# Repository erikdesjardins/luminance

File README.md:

# luminance

AKA "light destroyer". High voltage switching current supply.

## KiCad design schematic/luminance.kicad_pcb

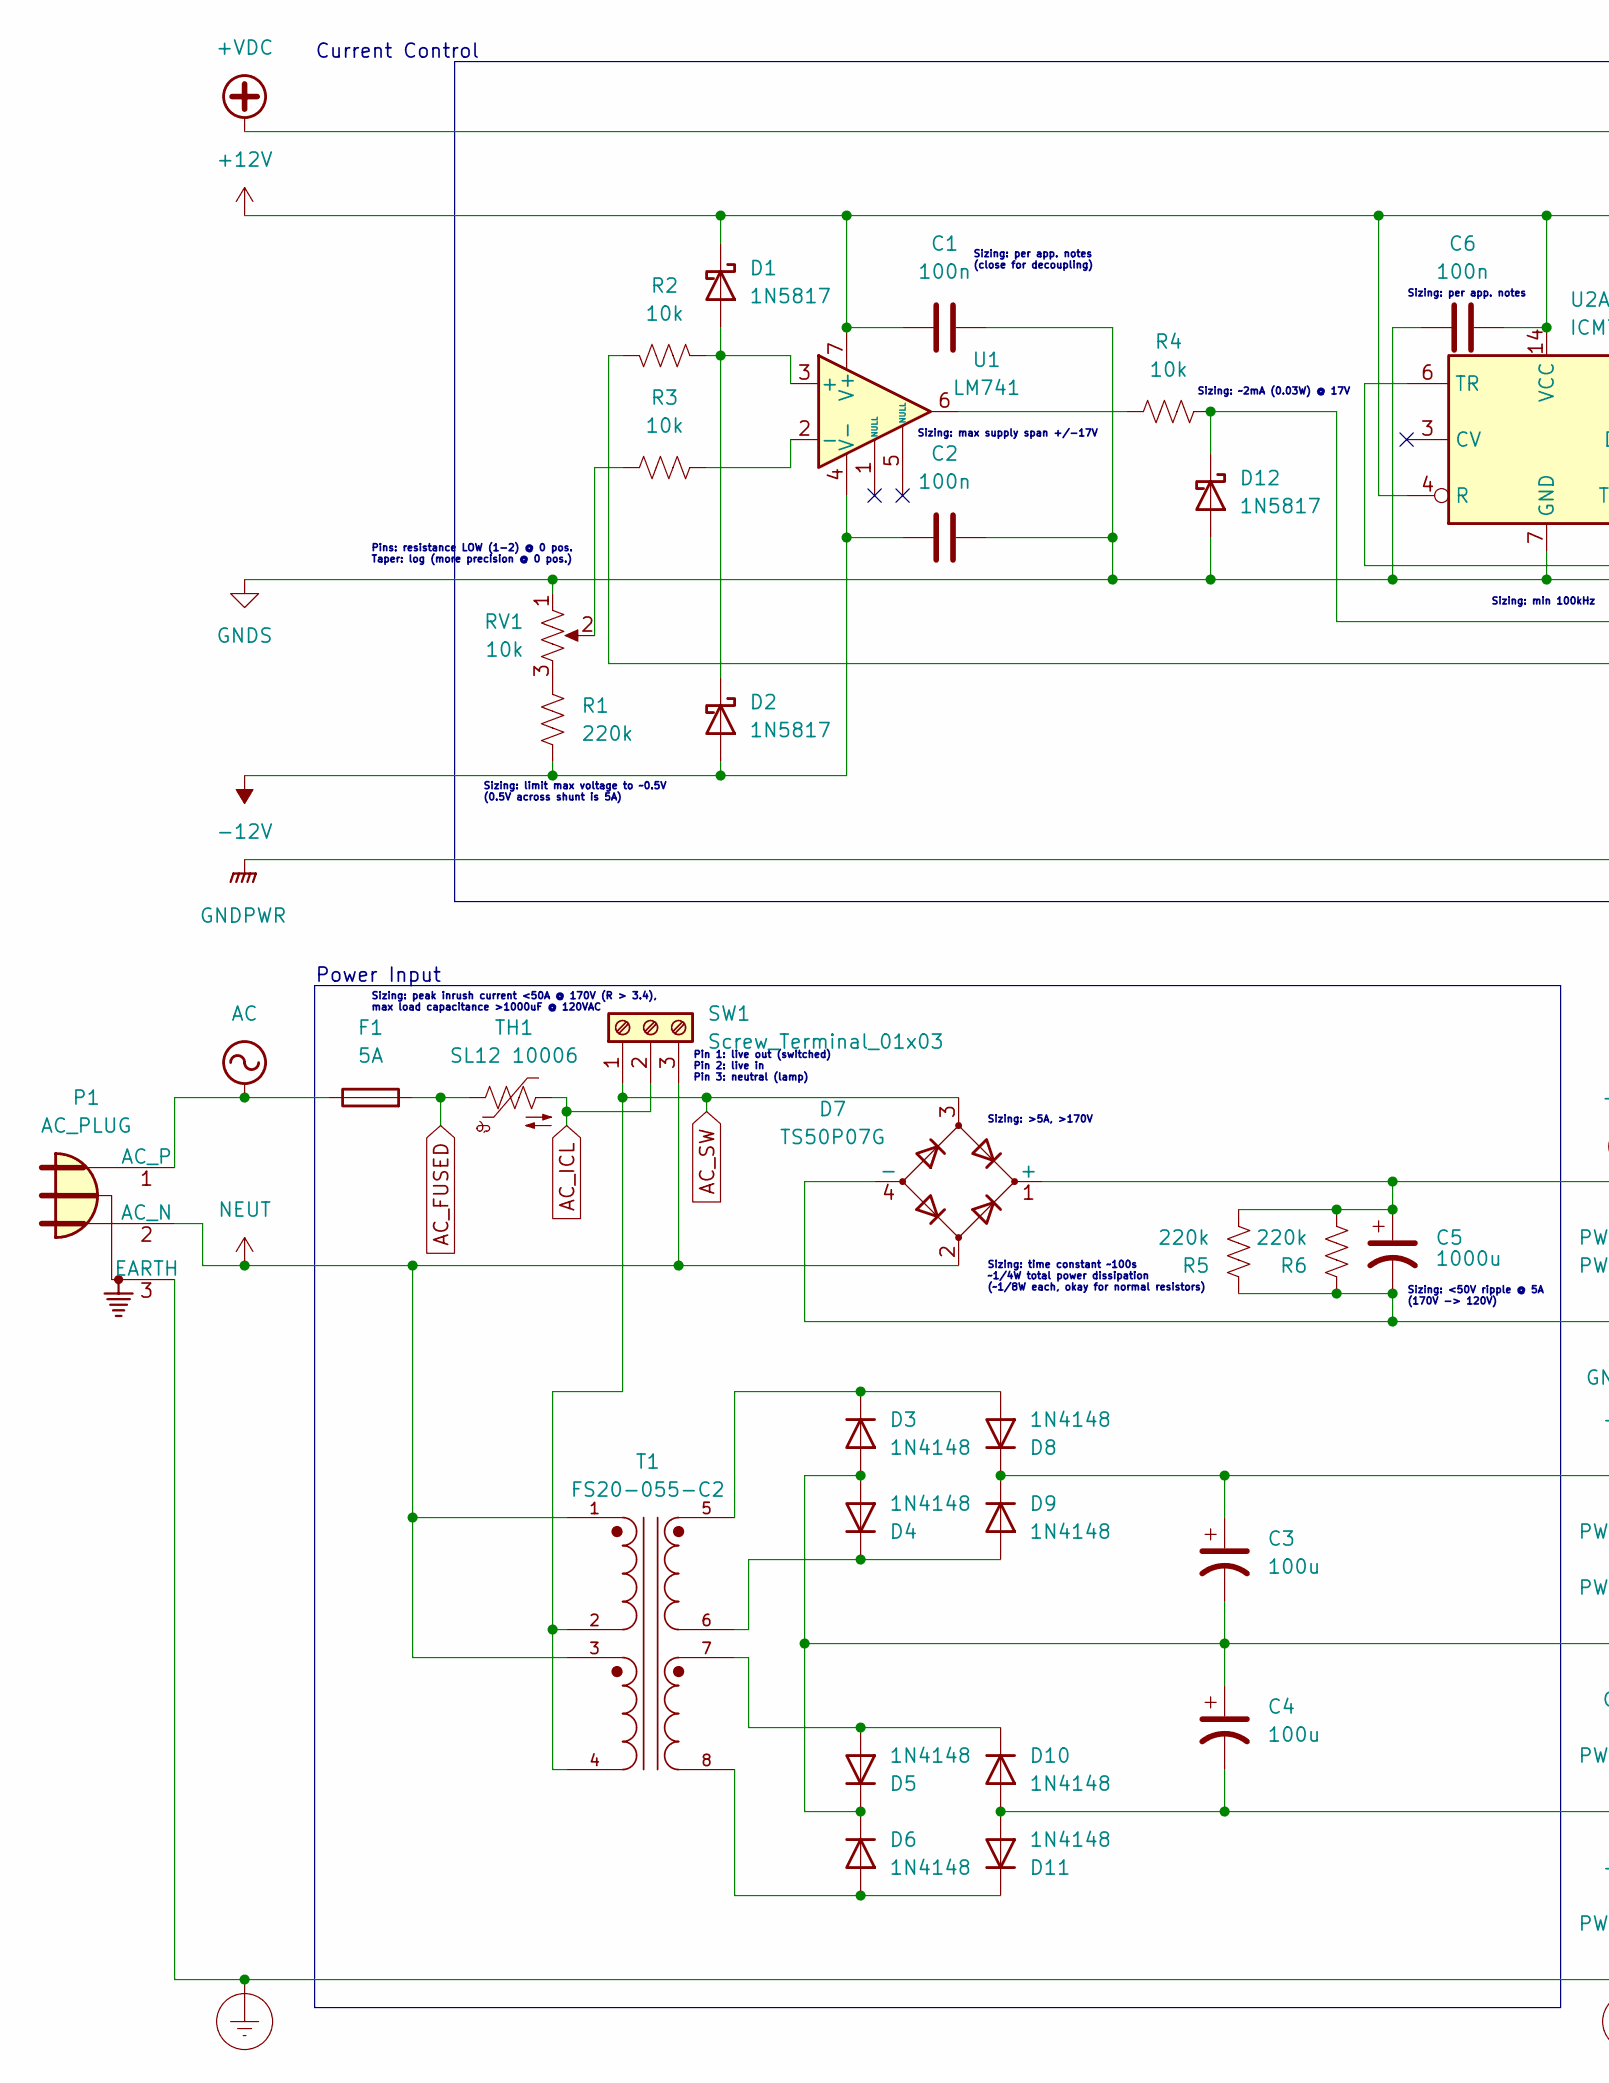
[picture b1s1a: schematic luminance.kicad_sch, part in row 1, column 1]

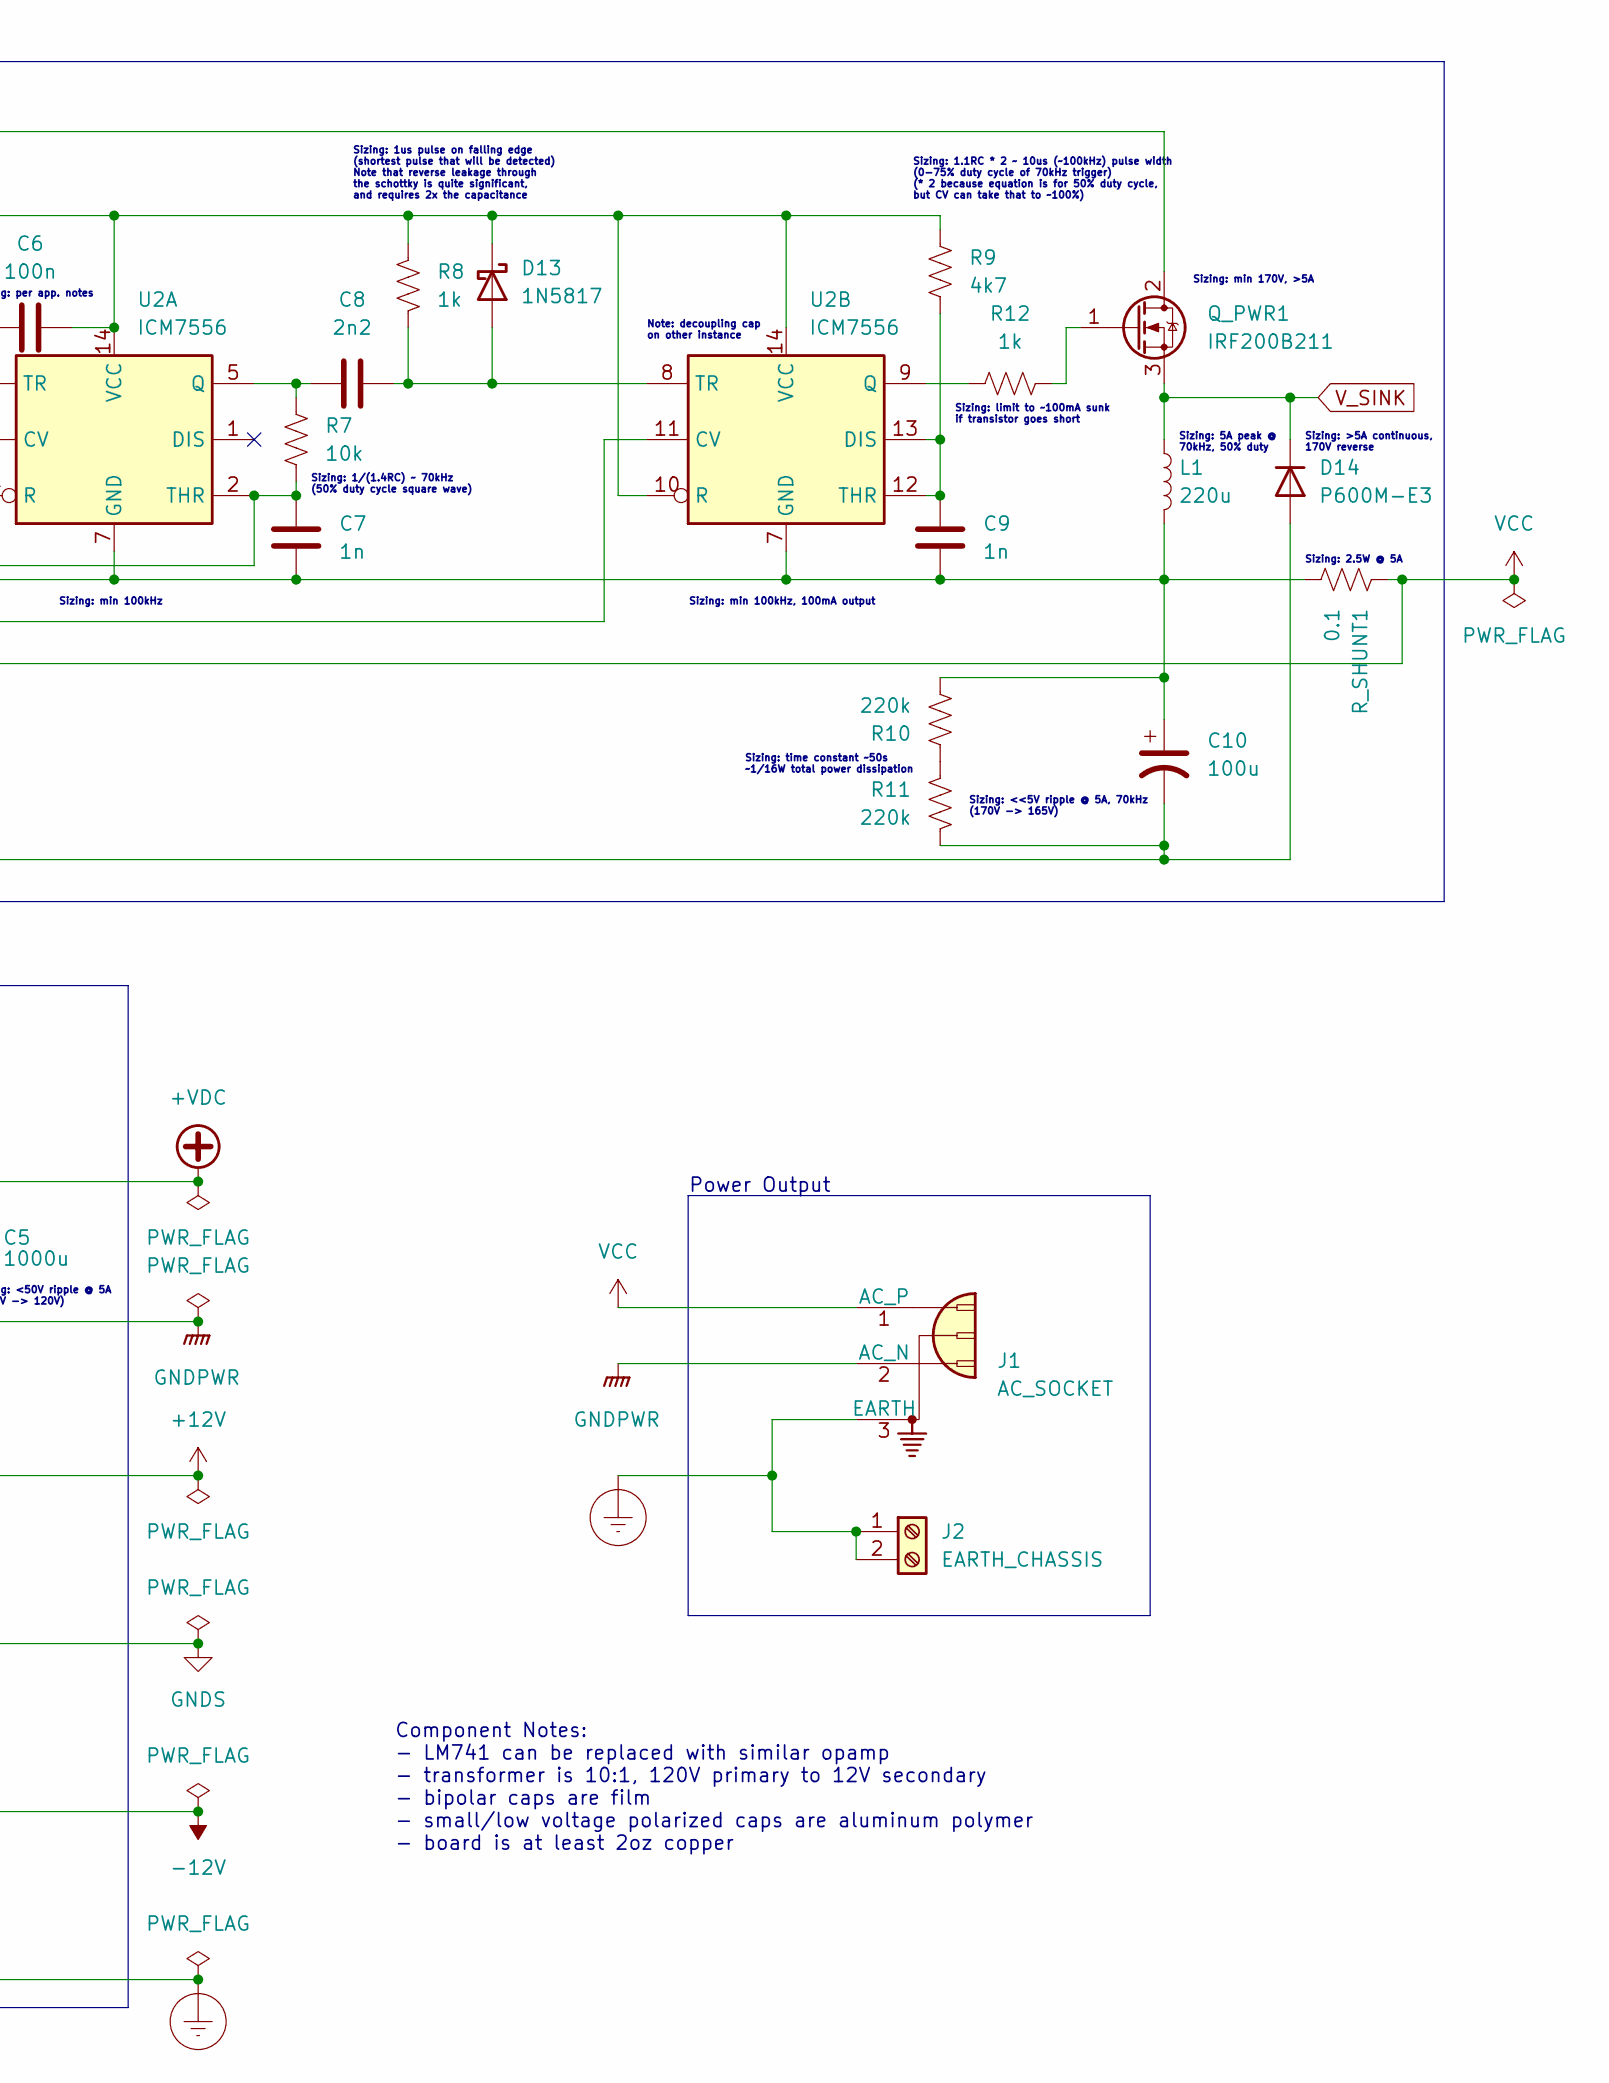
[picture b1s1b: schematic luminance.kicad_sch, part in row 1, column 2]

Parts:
C1, C2, C6: 100n; C_Rect_L7.2mm_W2.5mm_P5.00mm_FKS2_FKP2_MKS2_MKP2
C3, C4: 100u; CP_Radial_D8.0mm_P3.50mm
C5: 1000u; CP_Radial_D30.0mm_P10.00mm_SnapIn
C7, C9: 1n; C_Rect_L7.2mm_W2.5mm_P5.00mm_FKS2_FKP2_MKS2_MKP2
C8: 2n2; C_Rect_L7.2mm_W2.5mm_P5.00mm_FKS2_FKP2_MKS2_MKP2
C10: 100u; CP_Radial_D16.0mm_P7.50mm
D1, D2, D12, D13: 1N5817; D_DO-41_SOD81_P10.16mm_Horizontal
D3, D4, D5, D6, D8, D9, D10, D11: 1N4148; D_DO-35_SOD27_P7.62mm_Horizontal
D7: TS50P07G; DIOB_TS50P07G
D14: P600M-E3; P600
F1: 5A; 696106003002
J1: AC_SOCKET; TerminalBlock_Phoenix_PT-1,5-3-5.0-H_1x03_P5.00mm_Horizontal
J2: EARTH_CHASSIS; TerminalBlock_Phoenix_PT-1,5-2-5.0-H_1x02_P5.00mm_Horizontal
L1: 220u; L_Toroid_Vertical_L31.8mm_W15.9mm_P13.50mm_Bourns_5700
P1: AC_PLUG; TerminalBlock_Phoenix_PT-1,5-3-5.0-H_1x03_P5.00mm_Horizontal
Q_PWR1: IRF200B211; TO-220-3_Vertical
R1, R5, R6, R10, R11: 220k; R_Axial_DIN0204_L3.6mm_D1.6mm_P7.62mm_Horizontal
R2, R3, R4, R7: 10k; R_Axial_DIN0204_L3.6mm_D1.6mm_P7.62mm_Horizontal
R8, R12: 1k; R_Axial_DIN0204_L3.6mm_D1.6mm_P7.62mm_Horizontal
R9: 4k7; R_Axial_DIN0204_L3.6mm_D1.6mm_P7.62mm_Horizontal
RV1: 10k; TerminalBlock_Phoenix_PT-1,5-3-5.0-H_1x03_P5.00mm_Horizontal
R_SHUNT1: 0.1; R_Shunt_Vishay_SR3_P15.24mm_Horizontal
SW1: Screw_Terminal_01x03; TerminalBlock_Phoenix_PT-1,5-3-5.0-H_1x03_P5.00mm_Horizontal
T1: FS20-055-C2; XFMR_FS20-055-C2; PARTREV N/A
TH1: SL12 10006; C_Disc_D12.5mm_W5.0mm_P7.50mm
U1: LM741; DIP-8_W7.62mm_Socket
U2: ICM7556; DIP-14_W7.62mm_Socket

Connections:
+12V: C1.2, C3.1, C6.2, D1.1 (K), D8.1 (K), D9.1 (K), D13.1 (K), R8.1, R9.1, U1.7 (V+), U2.4 (R), U2.10 (R), U2.14 (VCC)
+VDC: C5.1, D7.1 (+), Q_PWR1.2 (D), R5.2, R6.2
-12V: C2.1, C4.2, D2.2 (A), D10.2 (A), D11.2 (A), R1.1, U1.4 (V-)
AC: F1.1, P1.1 (AC_P)
AC_FUSED: F1.2, TH1.1
AC_ICL: SW1.2, TH1.2
AC_SW: D7.3, SW1.1, T1.2, T1.4
Earth_Protective: J1.3 (EARTH), J2.1, J2.2, P1.3 (EARTH)
GNDPWR: C5.2, C10.2, D7.4 (-), D14.2 (A), J1.2 (AC_N), R5.1, R6.1, R11.2
GNDS: C1.1, C2.2, C3.2, C4.1, C6.1, C7.1, C9.2, C10.1, D3.2 (A), D4.2 (A), D5.1 (K), D6.1 (K), D12.2 (A), L1.2, R10.2, RV1.1, R_SHUNT1.2, U2.7 (GND)
NEUT: D7.2, P1.2 (AC_N), SW1.3, T1.1, T1.3
unnamed: C7.2, R7.1, U2.2 (THR), U2.6 (TR)
unnamed: C8.1, D13.2 (A), R8.2, U2.8 (TR)
unnamed: C8.2, R7.2, U2.5 (Q)
unnamed: C9.1, R9.2, U2.12 (THR), U2.13 (DIS)
unnamed: D1.2 (A), D2.1 (K), R2.1, U1.3 (+)
unnamed: D3.1 (K), D8.2 (A), T1.5
unnamed: D4.1 (K), D9.2 (A), T1.6
unnamed: D5.2 (A), D10.1 (K), T1.7
unnamed: D6.2 (A), D11.1 (K), T1.8
unnamed: D12.1 (K), R4.1, U2.11 (CV)
unnamed: Q_PWR1.1 (G), R12.1
unnamed: R1.2, RV1.3
unnamed: R3.1, U1.2 (-)
unnamed: R3.2, RV1.2
unnamed: R4.2, U1.6
unnamed: R10.1, R11.1
unnamed: R12.2, U2.9 (Q)
VCC: J1.1 (AC_P), R2.2, R_SHUNT1.1
V_SINK: D14.1 (K), L1.1, Q_PWR1.3 (S)

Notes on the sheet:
Sizing: min 170V, >5A
Component Notes: - LM741 can be replaced with similar opamp - transformer is 10:1, 120V primary to 12V secondary - bipolar caps are film - small/low voltage polarized caps are aluminum polymer - board is at least 2oz copper
Sizing: per app. notes
Sizing: limit to ~100mA sunk if transistor goes short
Sizing: >5A continuous, 170V reverse
Sizing: ~2mA (0.03W) @ 17V
Sizing: max supply span +/-17V
Power Output
Sizing: 1/(1.4RC) ~ 70kHz (50% duty cycle square wave)
Pins: resistance LOW (1-2) @ 0 pos. Taper: log (more precision @ 0 pos.)
Current Control
Sizing: 5A peak @ 70kHz, 50% duty
Power Input
Sizing: per app. notes (close for decoupling)
Sizing: <<5V ripple @ 5A, 70kHz (170V -> 165V)
Sizing: >5A, >170V
Sizing: min 100kHz
Sizing: 1us pulse on falling edge (shortest pulse that will be detected) Note that reverse leakage through the schottky is quite significant, and requires 2x the capacitance
Pin 1: live out (switched) Pin 2: live in Pin 3: neutral (lamp)
Sizing: peak inrush current <50A @ 170V (R > 3.4), max load capacitance >1000uF @ 120VAC
Sizing: 1.1RC * 2 ~ 10us (~100kHz) pulse width (0-75% duty cycle of 70kHz trigger) (* 2 because equation is for 50% duty cycle, but CV can take that to ~100%)
Sizing: time constant ~100s ~1/4W total power dissipation (~1/8W each, okay for normal resistors)
Sizing: 2.5W @ 5A
Sizing: <50V ripple @ 5A (170V -> 120V)
Note: decoupling cap on other instance
Sizing: time constant ~50s ~1/16W total power dissipation
Sizing: limit max voltage to ~0.5V (0.5V across shunt is 5A)
Sizing: min 100kHz, 100mA output

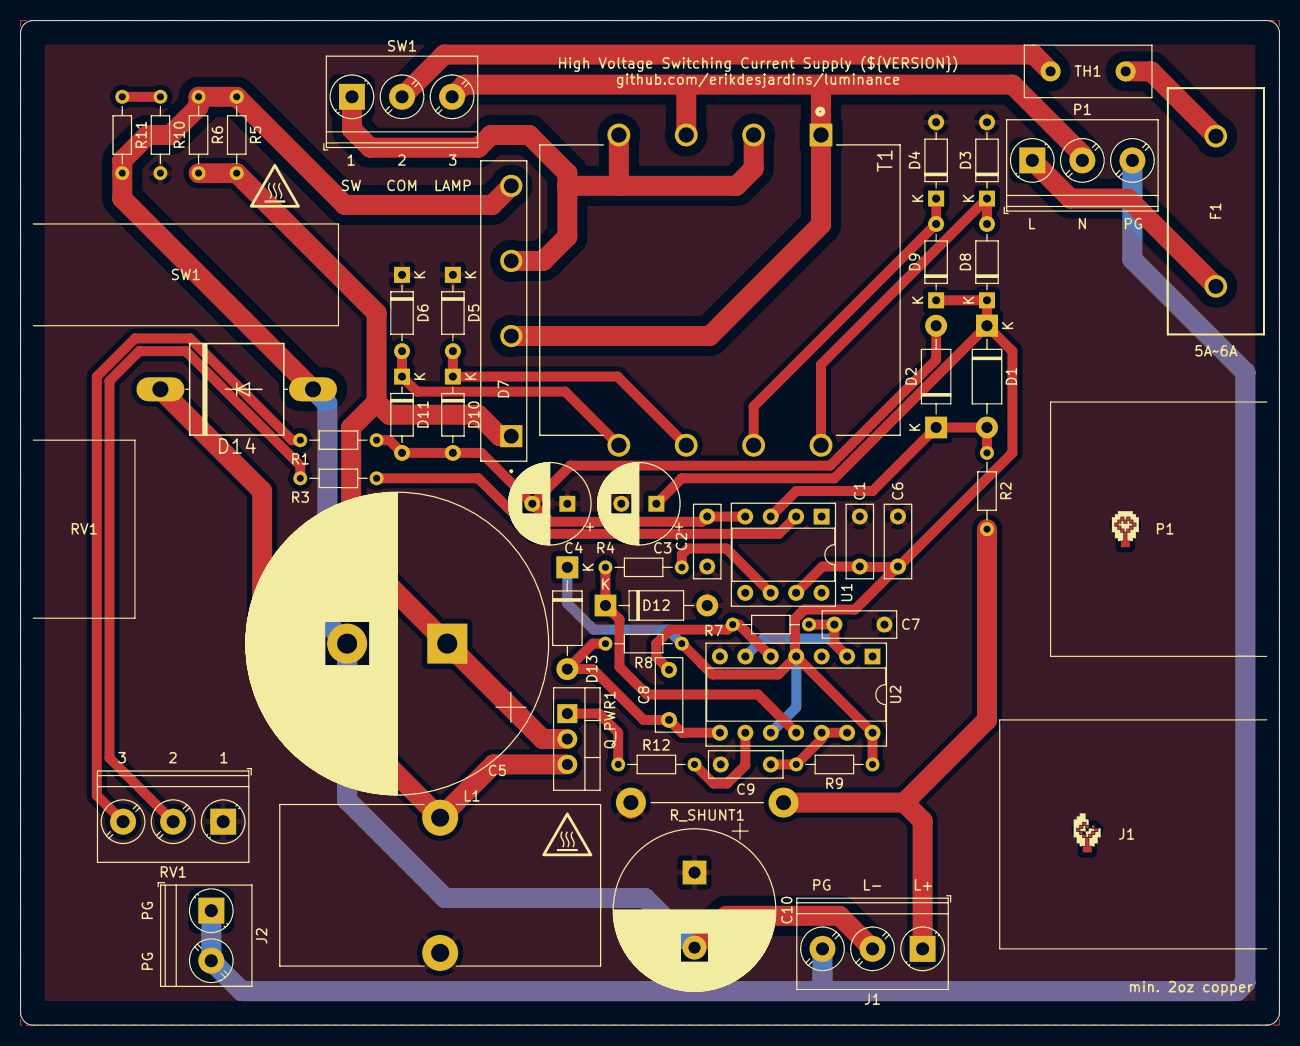
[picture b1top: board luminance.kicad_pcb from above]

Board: 2 copper layers, 125.7 x 100.3 mm, 49 parts (0 on the bottom side), 30 nets.

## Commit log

2022-12-20 init kicad project
2022-12-20 initial schematic
2022-12-20 reduce shunt resistance by 10x to reduce power dissipation
2022-12-21 add footprints for everything but power transistor
2022-12-23 use split supply for the opamp
    ...since we have two secondaries on the transformer anyways.
    This will keep the signal well within the common-mode voltage range.
2022-12-23 better opamp input protection
    clamping shottkys on both inputs, and resistors to limit overvoltage
    current
    (these should never actually be useful, but might as well, since it's
    _sort of_ exposed to the outside world)
2022-12-23 add footprints for both BJT and MOSFET
    both seem to work, so might as well make footprints for both
    and just populate one
2022-12-24 fix weird courtyard for fuse holder
2022-12-24 initial pcb layout
2022-12-24 tweak routing
2022-12-24 use 0.1ohm current shunt instead of 0.01ohm
    the latter is just too small, it's on the order of the trace resistance,
    so we don't really get a good signal
    this does limit us to 5A due to power dissipation in the shunt, which
    should be fine
2022-12-24 route sensitive pot traces away from the transformer
2022-12-24 add power ground copper fill on top as well
    partly to help shield the transformer, partly to make power ground
    connections even lower impedance
2022-12-24 tweak some component positions for better pwrground fill
2022-12-24 move cap discharge resistor out of the way
    this is going to be dissipating heat constantly, so we should move it
    away from other heat-generating components (current shunt, transistor)
    this also lets us get a bit better fill for the downstream side of the
    current shunt
2022-12-24 add filtering cap across pot
2022-12-24 add silkscreen for terminal blocks and fuse size
2022-12-24 add version text and global variable
2022-12-24 add small corner radii to board outline
2022-12-24 add lightbulb pixel art
2023-01-06 fix diode bridge footprint
    the holes were too small
2023-01-06 swap direction of transformer primary windings
    this lets us use slightly shorter traces to feed it, and gets better
    ground fill under the transformer
2023-01-06 make thermal reliefs use 1mm traces
    doubled from 0.5mm, for more current-carrying capability
2023-01-06 increase default track width to 1mm
    ...for reduced impedance
    in some places we are measuring very small voltages, so this may
    actually matter
2023-01-07 add neutral pin for lamp in switch
    turns out you need somewhere for the current to flow for a lamp to work.
    oops.
2023-01-07 tweak terminal blocks positions for a bit more room
2023-01-07 set default layer to silk
    this is useful for a final check that terminal block labels, version,
    etc. are correct
2023-01-07 heavily improve layout
    - Remove discharging resistors on 12V caps
    It's okay if the opamp stays powered, and the caps are charged to safe
    voltages anyways so they don't need to be discharged.
    - Replace discharging power resistor on big caps with jellybean res
    We only need to dissipate ~1/2W total, which is easy to do with a few
    normal 1/4W resistors, avoiding a special power resistor.
2023-01-08 remove BJT footprint
    a MOSFET works fine, with less power consumption, and cheaper
2023-01-08 remove one large cap
    we only need 1000uF to limit ripple to 50V (170V->120V)
    at max 5A current draw
    as a result, we get a lot more board space. use it to add more clearance
    for the MOSFET (which will need a heatsink)
2023-01-08 add heatsink for mosfet and heat warning icons
2023-01-08 set thermal reliefs back to 0.5mm/0.5mm
    With the two sided power plane:
    2 sides * 4 spokes * 0.5mm = 4mm
    ...which is the trace width we use for power traces.
    The 1mm we switched to was overkill.
    (0.5mm is hard enough to solder, I'm afraid 1mm would be nearly
    impossible.)
2023-01-08 call it a linear power supply, which it is
2023-01-08 add notes about using 2oz copper
2023-01-08 update symbols from library to fix ERC warning
2023-03-27 initial conversion to switch mode power supply
    linear regulators have fundamental limits (power dissipations in the
    transistor), so switch (heh) to a switcher
    also, add an inrush current limiting NTC resistor, to eliminate the
    frequent fuse blows on startup i'm seeing with the current design
    also, decrease the width of power tracks. the previous was massively
    overkill.
2023-03-27 remove input protection zeners from pot
    it's just a voltage divider, it can't go beyond the rails
    (except a tiny bit with the cap at shutdown, but that should be fine)
    this frees up a lot of space, allowing us to move the shunt out of the
    way
2023-03-27 move some pwrgnd to front copper
    this makes the main (rear) ground place more contiguous
2023-03-28 switch to 7556 dual 555
    this saves space, which is already at a premium
2023-03-28 remove filter cap across pot
    this shouldn't be necessary
2023-04-02 add heat warning near discharge resistors; tweak routing
2023-04-03 use schottky for edge detection on 555 output
    in practice, this reduces the spike from ~1V over V+ to 0.5V,
    which is quite significant
    this might be why `annoyance` doesn't work quite right sometimes...
2023-04-03 double capacitance for 555 edge detection
    as i discovered when applying the schottky change from the previous
    commit to `annoyance`, there is quite a lot of reverse leakage, enough
    to greatly shorten the pulse and break pulse detection with the current
    1nF. double up the cap to prevent this
2023-04-03 remove direct traces between output inductor, cap, and shunt
    there is already a ground plane here, so this means there's no
    clearance, i.e. it creates a huge connection where there should be a
    thermal relief
    components are hard enough to solder even with these thermal reliefs,
    having a solid trace go straight into the ground plane would make it
    impossible
2023-06-04 halve discharge resistor on PWM 555 timer
    the usual 1.1RC pulse width formula for 555 timers is for the usual 50%
    duty cycle, but since i'm modulating CV that can get up to ~100%, so i
    was off by a factor of 2
2023-06-04 change opamp input resistors 1k -> 10k
    This seems to result in a bit less (but still not zero) oscillation.
    Also, since one of these inputs is basically exposed to the outside
    world, using a bigger resistor can't hurt.
2023-06-04 fix silkscreen overlap
2023-06-15 move some tracks to improve ground plane connectivity a bit
2023-06-17 add 1k resistor on transistor gate to protect 555
    as it turns out, this design currently destroys the transistor on
    startup, and shorting the output of a 555 to line voltage is a good way
    to destroy it too...
